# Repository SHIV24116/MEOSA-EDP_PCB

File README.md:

# Bhoomi Shiv (EDP) — KiCad PCB

A fully validated 2-layer KiCad 10 PCB design for the **Bhoomi Shiv** agricultural IoT device,
part of the **MEOSA EDP** project.

## Board Specifications
- **Dimensions**: 110 mm × 100 mm, 2-layer
- **MCU**: ESP32-S3 DevKitC-1 N16R8 (mounted via dual 1×22 female pin sockets)
- **Power**: 1S2P Li-ion battery → TP4056 charger → MT3608 5V boost → 1N5819 Schottky protection
- **Peripherals**:
  - Soil Moisture Sensor (JST-XH 3-pin)
  - DS18B20 Waterproof Temperature Probe (JST-XH 3-pin, 1-Wire with 4.7k pull-up)
  - SSD1306 0.96" I2C OLED Display (JST-XH 4-pin)
  - AS7265x Triad Spectral Sensor (JST-XH 4-pin, shared I2C bus)
  - Piezo Buzzer with 2N2222 NPN driver & 1N4148 flyback diode (JST-XH 2-pin)
  - User tactile test button with hardware debounce (10k PU, 1k series, 100nF filter)
- **External Charge Input**: JST-XH 2-pin 5V USB input → TP4056

## Verification Status
| Check | Result |
|---|---|
| ERC (Electrical Rules Check) | ✅ 0 Errors |
| DRC (Design Rules Check) | ✅ 0 Violations |
| Unconnected Items | ✅ 0 |
| Ground Plane (B.Cu) | ✅ Continuous solid GND pour |

## Project Files
| File | Description |
|---|---|
| `Bhoomi_shiv(edp).kicad_pro` | KiCad 10 Project |
| `Bhoomi_shiv(edp).kicad_sch` | Full Schematic |
| `Bhoomi_shiv(edp).kicad_pcb` | PCB Layout |
| `BOM_Bhoomi_shiv.csv` | Bill of Materials |
| `drc_report.rpt` | DRC Verification Report |
| `erc_report.rpt` | ERC Verification Report |
| `render_top.png` | 3D Top View |
| `render_bot.png` | 3D Bottom View |
| `gerbers/` | Gerber + Excellon drill files for fabrication |

## Manufacturing
Send the `gerbers/` folder to JLCPCB / PCBWay / any fab house.
- **Layers**: 2
- **Board size**: 110 × 100 mm
- **Min trace/space**: 0.25 mm / 0.25 mm
- **Drill**: Excellon format, included in `gerbers/`
- **Surface finish**: HASL or ENIG recommended

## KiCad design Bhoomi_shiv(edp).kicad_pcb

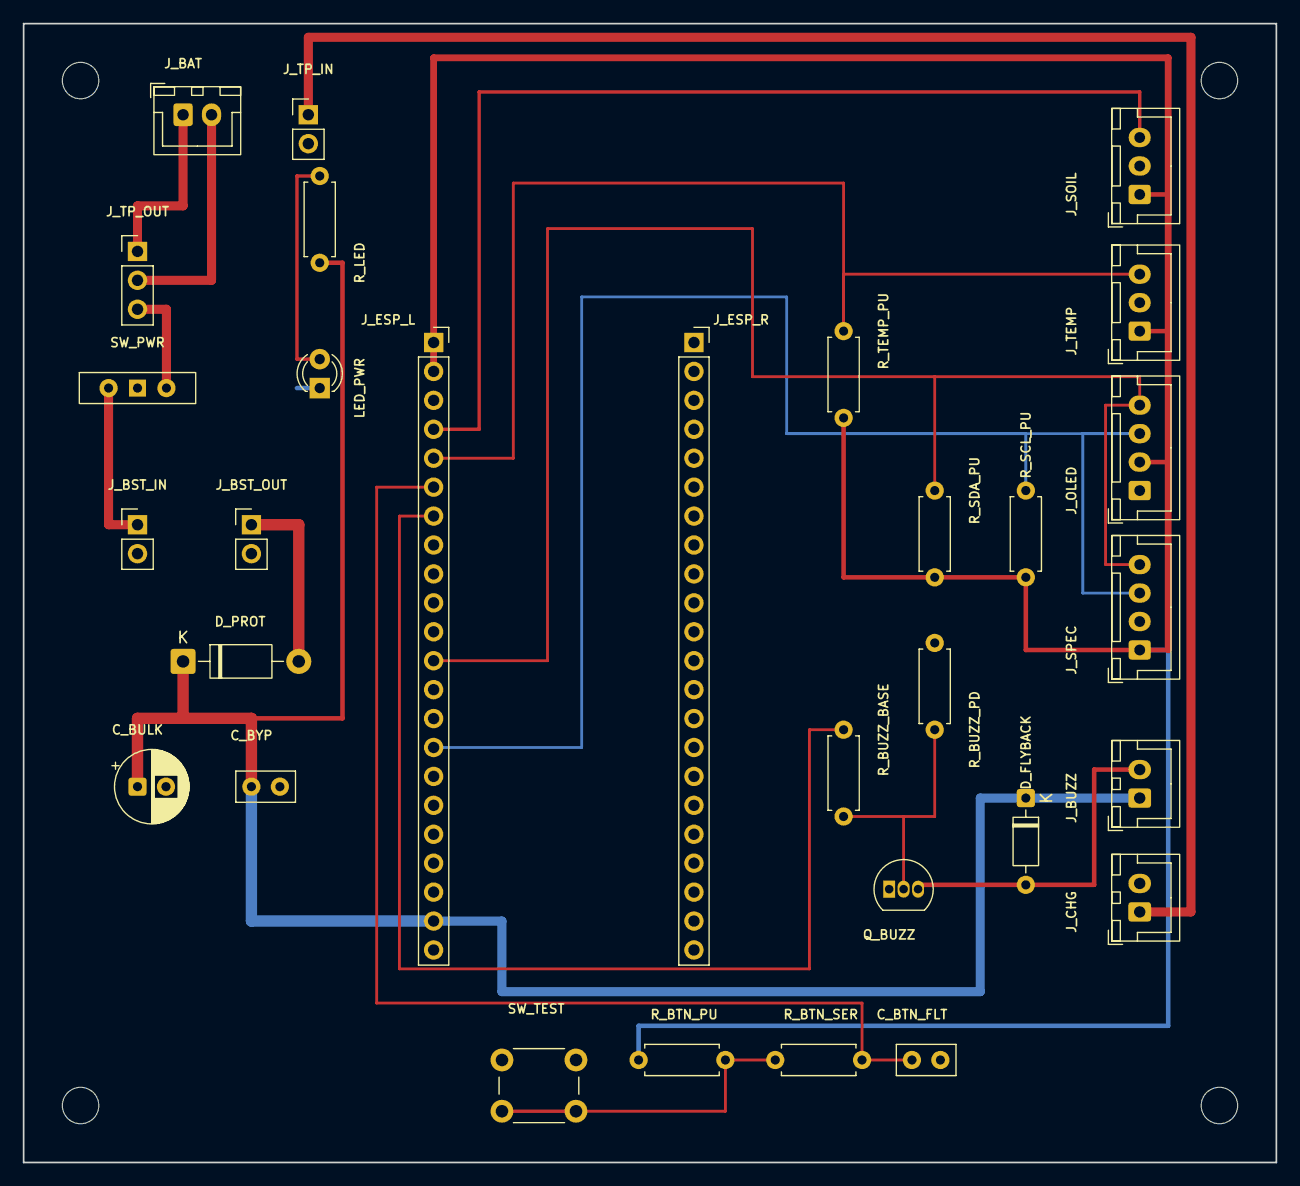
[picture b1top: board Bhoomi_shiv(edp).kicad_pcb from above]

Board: 2 copper layers, 110.0 x 100.0 mm, 34 parts (0 on the bottom side), 19 nets.

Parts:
C_BTN_FLT: 100nF; C_Disc_D5.0mm_W2.5mm_P2.50mm
C_BULK: 100uF/16V; CP_Radial_D6.3mm_P2.50mm
C_BYP: 100nF; C_Disc_D5.0mm_W2.5mm_P2.50mm
D_FLYBACK: 1N4148; D_DO-35_SOD27_P7.62mm_Horizontal
D_PROT: 1N5819; D_DO-41_SOD81_P10.16mm_Horizontal
J_BAT: 1S2P_Battery; JST_XH_B2B-XH-A_1x02_P2.50mm_Vertical
J_BST_IN: MT3608_IN; PinHeader_1x02_P2.54mm_Vertical
J_BST_OUT: MT3608_OUT; PinHeader_1x02_P2.54mm_Vertical
J_BUZZ: Buzzer_Port; JST_XH_B2B-XH-A_1x02_P2.50mm_Vertical
J_CHG: USB_Charge_In; JST_XH_B2B-XH-A_1x02_P2.50mm_Vertical
J_ESP_L: ESP32_S3_J1; PinSocket_1x22_P2.54mm_Vertical
J_ESP_R: ESP32_S3_J3; PinSocket_1x22_P2.54mm_Vertical
J_OLED: SSD1306_OLED; JST_XH_B4B-XH-A_1x04_P2.50mm_Vertical
J_SOIL: Soil_Moisture; JST_XH_B3B-XH-A_1x03_P2.50mm_Vertical
J_SPEC: AS7265x_Triad; JST_XH_B4B-XH-A_1x04_P2.50mm_Vertical
J_TEMP: DS18B20_Probe; JST_XH_B3B-XH-A_1x03_P2.50mm_Vertical
J_TP_IN: TP4056_VIN; PinHeader_1x02_P2.54mm_Vertical
J_TP_OUT: TP4056_BAT; PinHeader_1x03_P2.54mm_Vertical
LED_PWR: Green_3mm; LED_D3.0mm
MH1, MH2, MH3, MH4: MountingHole_3.2mm_M3
Q_BUZZ: 2N2222; TO-92_Inline
R_BTN_PU: 10k; R_Axial_DIN0207_L6.3mm_D2.5mm_P7.62mm_Horizontal
R_BTN_SER: 1k; R_Axial_DIN0207_L6.3mm_D2.5mm_P7.62mm_Horizontal
R_BUZZ_BASE: 1k; R_Axial_DIN0207_L6.3mm_D2.5mm_P7.62mm_Horizontal
R_BUZZ_PD: 100k; R_Axial_DIN0207_L6.3mm_D2.5mm_P7.62mm_Horizontal
R_LED: 1k; R_Axial_DIN0207_L6.3mm_D2.5mm_P7.62mm_Horizontal
R_SCL_PU: 4.7k; R_Axial_DIN0207_L6.3mm_D2.5mm_P7.62mm_Horizontal
R_SDA_PU: 4.7k; R_Axial_DIN0207_L6.3mm_D2.5mm_P7.62mm_Horizontal
R_TEMP_PU: 4.7k; R_Axial_DIN0207_L6.3mm_D2.5mm_P7.62mm_Horizontal
SW_PWR: Master_Power; SW_Slide-03_Wuerth-WS-SLTV_10x2.5x6.4_P2.54mm
SW_TEST: Test_Button; SW_PUSH_6mm

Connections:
+3V3: J_ESP_L.1, J_ESP_L.2, J_OLED.2, J_SOIL.1, J_SPEC.1, J_TEMP.1, R_BTN_PU.1, R_SCL_PU.2, R_SDA_PU.2, R_TEMP_PU.2
+5V_PROT: C_BULK.1, C_BYP.1, D_FLYBACK.1, D_PROT.1, J_BUZZ.1, J_ESP_L.21, R_LED.1
BTN_FILTERED: C_BTN_FLT.1, J_ESP_L.6, R_BTN_SER.2
BTN_MID: R_BTN_PU.2, R_BTN_SER.1, SW_TEST.2
BUZZER_PWM: J_ESP_L.7, R_BUZZ_BASE.1
BUZZ_COLL: D_FLYBACK.2, J_BUZZ.2, Q_BUZZ.3
EXT_5V_CHG: J_CHG.1, J_TP_IN.1
GND: C_BTN_FLT.2, C_BULK.2, C_BYP.2, J_BST_IN.2, J_BST_OUT.2, J_CHG.2, J_ESP_L.22, J_ESP_R.1, J_ESP_R.21, J_ESP_R.22, J_OLED.1, J_SOIL.2, J_SPEC.2, J_TEMP.2, J_TP_IN.2, LED_PWR.1, Q_BUZZ.1, R_BUZZ_PD.2, SW_TEST.1
I2C_SCL: J_ESP_L.15, J_OLED.3, J_SPEC.3, R_SCL_PU.1
I2C_SDA: J_ESP_L.12, J_OLED.4, J_SPEC.4, R_SDA_PU.1
LED_A: LED_PWR.2, R_LED.2
ONEWIRE_DATA: J_ESP_L.5, J_TEMP.3, R_TEMP_PU.1
Q_BASE: Q_BUZZ.2, R_BUZZ_BASE.2, R_BUZZ_PD.1
SOIL_AOUT: J_ESP_L.4, J_SOIL.3
VBAT+: J_BAT.1, J_TP_OUT.1
VBAT-: J_BAT.2, J_TP_OUT.2
V_BAT_SW: J_BST_IN.1, SW_PWR.2
V_BAT_UNSW: J_TP_OUT.3, SW_PWR.3
V_BOOST_5V3: D_PROT.2, J_BST_OUT.1
